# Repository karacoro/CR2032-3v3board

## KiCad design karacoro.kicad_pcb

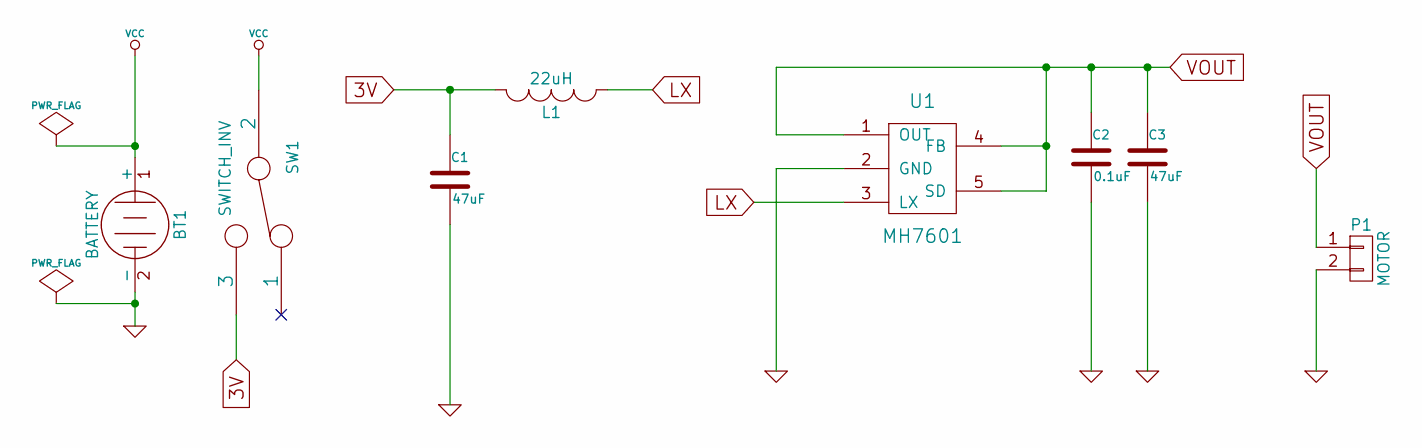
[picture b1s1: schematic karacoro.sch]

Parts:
BT1: BATTERY; STL2032HLD-A
C1, C3: 47uF; R_2816_HandSoldering
C2: 0.1uF; C_1206_HandSoldering
L1: 22uH; CD32
P1: MOTOR; Pin_Header_Straight_2x01_Pitch2.54mm
SW1: SWITCH_INV; SW_SPDT_PCM12
U1: MH7601; SOT-23-5

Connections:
3V: C1.1, L1.2, SW1.3
GND: BT1.2 (-), C1.2, C2.2, C3.2, P1.2, U1.2 (GND)
LX: L1.1, U1.3 (LX)
VCC: BT1.1 (+), SW1.2
VOUT: C2.1, C3.1, P1.1, U1.1 (OUT), U1.4 (FB), U1.5 (SD)

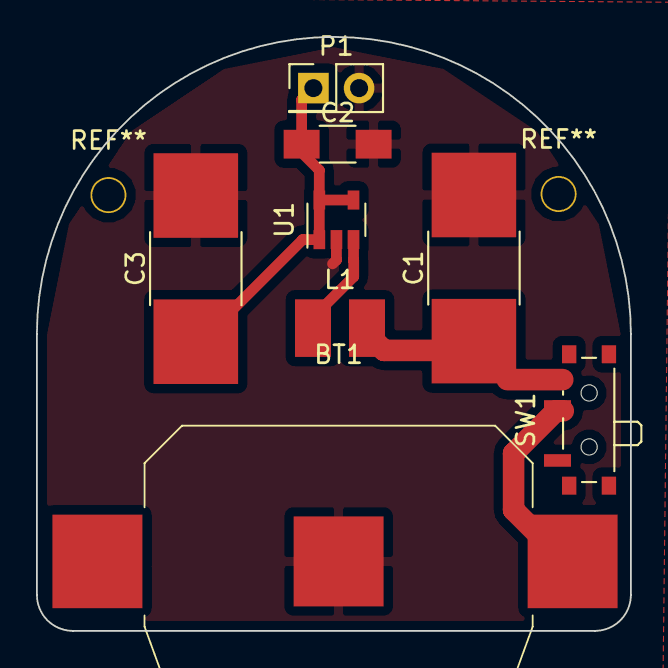
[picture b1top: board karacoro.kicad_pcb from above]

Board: 2 copper layers, 33.0 x 33.0 mm, 8 parts (0 on the bottom side), 5 nets.

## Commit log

2018-02-17 commit.
2018-02-17 リソース追加
2018-05-23 pcb2gcode 設定ファイル更新
